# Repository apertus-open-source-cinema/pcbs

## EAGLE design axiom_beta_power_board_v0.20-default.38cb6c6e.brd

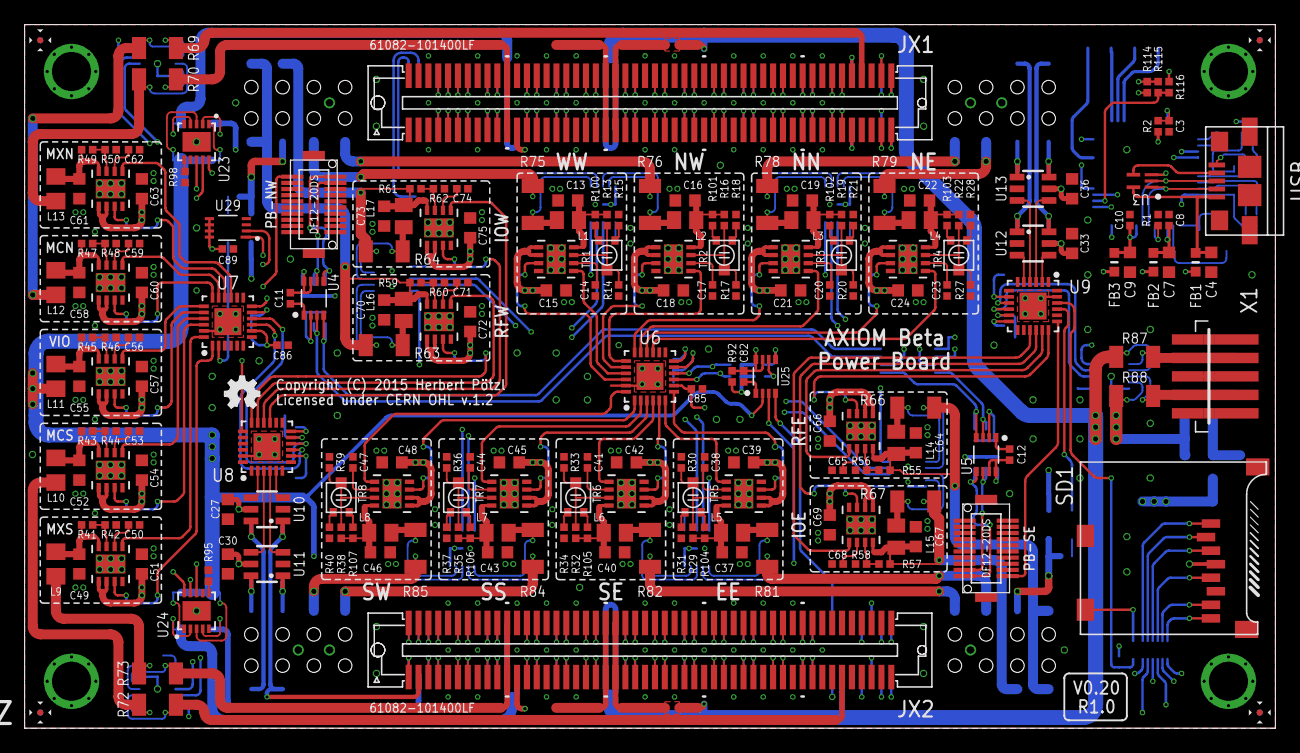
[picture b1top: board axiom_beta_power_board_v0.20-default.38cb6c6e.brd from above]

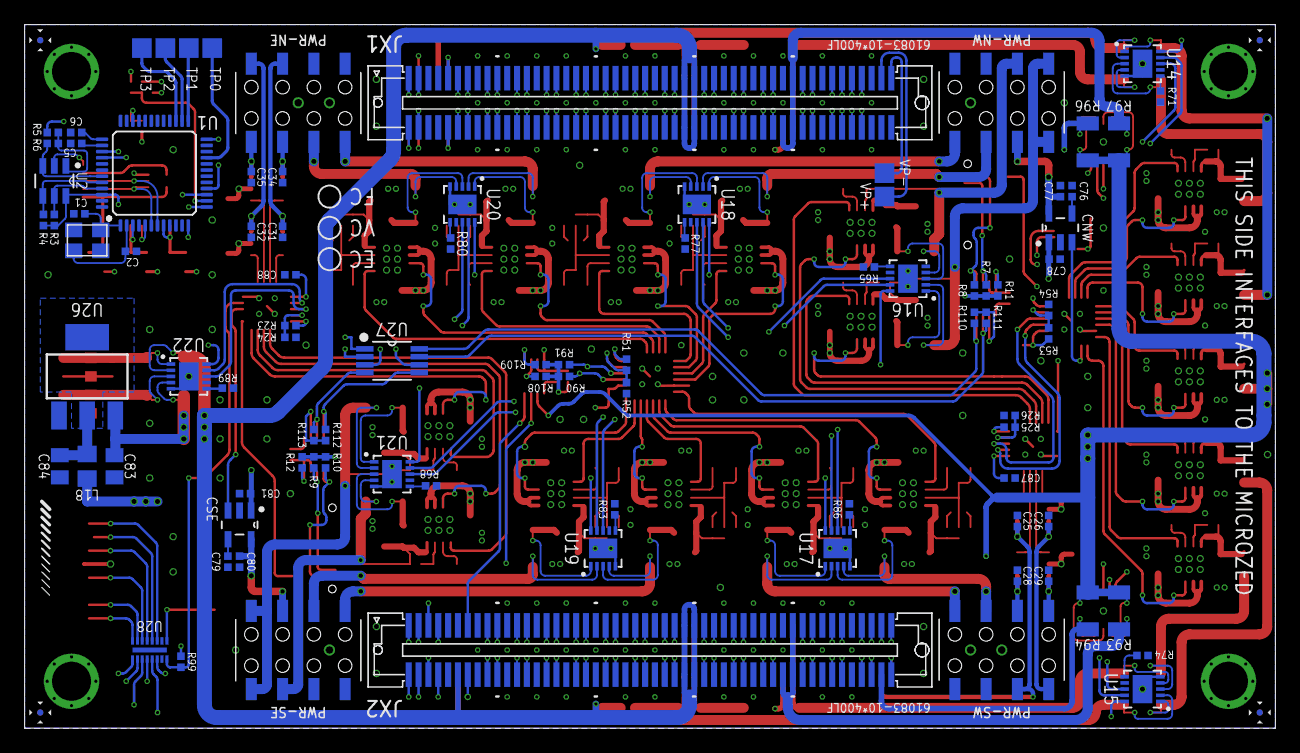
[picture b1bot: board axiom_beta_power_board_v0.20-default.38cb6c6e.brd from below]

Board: 4 copper layers, 101.6 x 57.1 mm, 301 parts (91 on the bottom side), 364 nets.

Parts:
BETA: µZ-FCI-SOCKET-NOHOLES-R; µZ-SOCKET-NOHOLES-R
C1, C2, C14, C17, C20, C23, C38, C41, C44, C47, C50, C53, C56, C59, C62, C65, C68, C71, C74: 0402-B
C3, C11, C12, C76, C79, C82: 10n; 0402-B
C4: 100n; 0603-B
C5, C6, C8, C10, C85, C86, C87, C88, C89: 100n; 0402-B
C7, C9, C27, C30, C33, C36: 4µ7; 0603-B
C13, C15, C16, C18, C19, C21, C22, C24, C37, C39, C40, C42, C43, C45, C46, C48, C49, C51, C52, C54, C55, C57, C58, C60, C61, C63, C64, C66, C67, C69, C73, C75: 0603-B
C25, C26, C28, C29, C31, C32, C34, C35, C77, C78, C80, C81: 1µ; 0402-B
C70, C72: 10µ; 0603-B
C83, C84: 22µ; 0805-B
CNW: SPX3819M5-L; SOT95P280X145-5N
CSE: SPX3819M5-L; SOT95P280X145-5N
EE: MCP1727-ADJE/MF; DFN65P300X300X100-9N
FB1, FB2, FB3: 600R; _0603MP
IOE: MCP1727-ADJE/MF; DFN65P300X300X100-9N
IOW: MCP1727-ADJE/MF; DFN65P300X300X100-9N
L1, L2, L3, L4, L5, L6, L7, L8, L14, L15, L16, L17: 0805-B
L9, L10, L11, L12, L13, L18: 0805-A
LOGO1: OSHW_LOGO_FILLX0100-NT; OSHW_FILLX100_NOTEXT
MCN: MCP1727-ADJE/MF; DFN65P300X300X100-9N
MCS: MCP1727-ADJE/MF; DFN65P300X300X100-9N
MXN: MCP1727-ADJE/MF; DFN65P300X300X100-9N
MXS: MCP1727-ADJE/MF; DFN65P300X300X100-9N
NE: MCP1727-ADJE/MF; DFN65P300X300X100-9N
NN: MCP1727-ADJE/MF; DFN65P300X300X100-9N
NW: MCP1727-ADJE/MF; DFN65P300X300X100-9N
PB-NW: DF12(XX)-20DP-0.5V
PB-SE: DF12(XX)-20DP-0.5V
PWR-NE: PINRC-2X04; R2X04
PWR-NW: PINRC-2X04; R2X04
PWR-SE: PINRC-2X04; R2X04
PWR-SW: PINRC-2X04; R2X04
Q1: SMD-4P-2G-3.2X2.5; ABM8G
R1: 12k; 0402-B
R2, R3, R4, R5, R24, R26, R99: 10k; 0402-B
R6: 2k; 0402-B
R7, R8, R9, R10, R90, R91, R108, R109, R110, R111, R112, R113: 4k7; 0402-B
R11, R12, R92: 200k; 0402-B
R13, R14, R15, R16, R17, R18, R19, R20, R21, R22, R27, R28, R29, R30, R31, R32, R33, R34, R35, R36, R37, R38, R39, R40, R41, R42, R43, R44, R45, R46, R47, R48, R49, R50, R55, R56, R57, R58, R59, R60, R61, R62, R100, R101, R102, R103, R104, R105, R106, R107: 0402-B
R23: 22k; 0402-B
R25, R51: 13k; 0402-B
R52: 3k; 0402-B
R53: 15k; 0402-B
R54: 1k; 0402-B
R63, R64, R66, R67, R69, R70, R72, R73, R75, R76, R78, R79, R81, R82, R84, R85, R87, R88, R93, R94, R96, R97: 1206-B
R65: 5k6; 0402-B
R68: 9k1; 0402-B
R71: 2k0; 0402-B
R74: 2k7; 0402-B
R77: 750R; 0402-B
R80: 1k27; 0402-B
R83, R114, R115, R116: 0R; 0402-B
R86: 100R; 0402-B
R89: 1k6; 0402-B
R95: 430R; 0402-B
R98: 560R; 0402-B
RFE: MCP1727-ADJE/MF; DFN65P300X300X100-9N
RFW: MCP1727-ADJE/MF; DFN65P300X300X100-9N
SD1: MICRO-SD-2CD; TF-MICRO-SD_PP2
SE: MCP1727-ADJE/MF; DFN65P300X300X100-9N
SS: MCP1727-ADJE/MF; DFN65P300X300X100-9N
SW: MCP1727-ADJE/MF; DFN65P300X300X100-9N
TP0, TP1, TP2, TP3: TPTP16SQ; TP16SQ
TR1, TR2, TR3, TR4, TR5, TR6, TR7, TR8: PVZ2A; TRIM-PVZ2A
U1: FT232H; LQFP48
U2: 93LC46BT-I/OT; SOT95P280X145-6N
U3: TPD3E001DRLR; SOT50P160X60-5N
U4, U5, U25: GTL2002DC; VSSOP-8
U6, U7, U8, U9: QFN50P400X400X80-25N
U10, U11, U12, U13: SOT23-6
U14, U15, U16, U17, U18, U19, U20, U21, U22, U23, U24: PAC1720; DFN3X3_10LEAD
U26: LD1117S; SOT-223
U27: PCA9540BDP; SOP65P490X110-8N
U28: IP4251CZ16-8-TTL; SON40P135X330X55-17N
U29: LM75BGD; SOT996-2/3
USB: 5_USB_3S; MICRO-AB-H-SMT
VIO: MCP1727-ADJE/MF; DFN65P300X300X100-9N
VP+: TPTP16SQ; TP16SQ
VP-: TPTP16SQ; TP16SQ
WW: MCP1727-ADJE/MF; DFN65P300X300X100-9N
X1: PICO-SPOX-5
ZED: µZ-FCI-CONONLY; µZ-CONONLY

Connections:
AB_SCL: U25.4, ZED.113
AB_SCL': R109.2, U25.5, U27.1
AB_SDA: U25.3, ZED.114
AB_SDA': R108.2, U25.6, U27.2
A_!SS: PB-NW.1, U8.19
A_SCL: PB-NW.2, R8.2, U4.5
A_SCL': R110.2, U4.4, U27.8
A_SDA: PB-NW.4, R7.2, U4.6
A_SDA': R111.2, U4.3, U27.7
BANK13_00_N: BETA.89, ZED.89
BANK13_00_P: BETA.87, ZED.87
BANK13_01_N: BETA.90, ZED.90
BANK13_01_P: BETA.88, ZED.88
BANK13_02_N: BETA.93, ZED.93
BANK13_02_P: BETA.91, ZED.91
BANK13_03_N: BETA.94, ZED.94
BANK13_03_P: BETA.92, ZED.92
BANK13_04_N: BETA.195, ZED.195
BANK13_04_P: BETA.193, ZED.193
BANK13_05_N: BETA.196, ZED.196
BANK13_05_P: BETA.194, ZED.194
BANK13_06_N: BETA.199, ZED.199
BANK13_06_P: BETA.197, ZED.197
BANK13_SE_0: BETA.200, ZED.200
BETA_5V: R88.1, U22.3, X1.4, X1.4A
BETA_5V': C15.1, C18.1, C21.1, C24.1, C27.1, C30.1, C33.1, C36.1, C39.1, C42.1, C45.1, C48.1, C51.1, C54.1, C57.1, C60.1, C63.1, C66.1, C69.1, C72.1, C75.1, C78.1, C81.1, C83.1, CNW.1, CSE.1, EE.1, EE.2, IOE.1, IOE.2, IOW.1, IOW.2, MCN.1, MCN.2, MCS.1, MCS.2, MXN.1, MXN.2, MXS.1, MXS.2, NE.1, NE.2, NN.1, NN.2, NW.1, NW.2, R88.2, RFE.1, RFE.2, RFW.1, RFW.2, SE.1, SE.2, SS.1, SS.2, SW.1, SW.2, U10.5, U11.5, U12.5, U13.5, U22.4, U26.3, VIO.1, VIO.2, WW.1, WW.2
BETA_TDI: BETA.4, R116.2
BETA_TDO: BETA.3, R114.1
B_!SS: PB-SE.1, U9.19
B_SCL: PB-SE.2, R10.2, U5.5
B_SCL': R112.2, U5.4, U27.5
B_SDA: PB-SE.4, R9.2, U5.6
B_SDA': R113.2, U5.3, U27.4
CD: SD1.CD1, U28.1
CD': R99.2, U9.22, U28.16
CLK: SD1.5, U28.6
CMD: SD1.3, U28.5
CNW_EN: CNW.3, U7.2
CSE_EN: CSE.3, U9.21
CSO_NE_V: BETA.7, R69.2, U14.2
CSO_NW_V: C77.1, CNW.5, PWR-NW.6
CSO_N_V': L12.2, R69.1, U14.1
CSO_SE_V: C80.1, CSE.5, PWR-SE.6
CSO_SW_V: BETA.112, R72.2, U15.2
CSO_S_V': L10.2, R72.1, U15.1
DAT0: SD1.7, U28.7
DAT1: SD1.8, U28.8
DAT2: SD1.1, U28.3
DAT3: SD1.2, U28.4
EE_CLK1: R4.1, U1.44, U2.4
EE_CS1: R3.1, U1.45, U2.5
EE_DATA1: R6.2, U1.43, U2.3
EE_EN: EE.3, U6.7
EE_PG: EE.5, U6.6
E_I2C_EN: U9.5, U12.3
E_I2C_V: C31.1, PWR-NE.6, U12.1
E_SPI_EN: U9.2, U12.4
E_SPI_V: C32.1, PWR-NE.8, U12.6
E_VE: PWR-SE.4, R81.2, U19.2
E_VE': L5.2, R81.1, U19.1
FTDI_D_N: U1.6, U3.1, USB.2
FTDI_D_P: U1.7, U3.2, USB.3
FTDI_TCK: BETA.1, U1.13, ZED.1
FTDI_TDI: R115.1, R116.1, U1.14
FTDI_TDO: U1.15, ZED.3
FTDI_TMS: BETA.2, U1.16, ZED.2
GND: BETA.15, BETA.16, BETA.21, BETA.22, BETA.27, BETA.28, BETA.33, BETA.34, BETA.39, BETA.40, BETA.45, BETA.46, BETA.51, BETA.52, BETA.65, BETA.66, BETA.71, BETA.72, BETA.77, BETA.85, BETA.86, BETA.95, BETA.96, BETA.115, BETA.116, BETA.121, BETA.122, BETA.127, BETA.128, BETA.133, BETA.134, BETA.139, BETA.140, BETA.145, BETA.146, BETA.151, BETA.152, BETA.165, BETA.166, BETA.171, BETA.172, BETA.177, BETA.185, BETA.186, BETA.191, BETA.192, C1.2, C2.2, C3.2, C4.2, C5.2, C6.2, C7.2, C8.2, C9.2, C10.2, C11.2, C12.2, C13.2, C14.2, C15.2, C16.2, C17.2, C18.2, C19.2, C20.2, C21.2, C22.2, C23.2, C24.2, C25.2, C26.2, C27.2, C28.2, C29.2, C30.2, C31.2, C32.2, C33.2, C34.2, C35.2, C36.2, C37.2, C38.2, C39.2, C40.2, C41.2, C42.2, C43.2, C44.2, C45.2, C46.2, C47.2, C48.2, C49.2, C50.2, C51.2, C52.2, C53.2, C54.2, C55.2, C56.2, C57.2, C58.2, C59.2, C60.2, C61.2, C62.2, C63.2, C64.2, C65.2, C66.2, C67.2, C68.2, C69.2, C70.2, C71.2, C72.2, C73.2, C74.2, C75.2, C76.2, C77.2, C78.2, C79.2, C80.2, C81.2, C82.2, C83.2, C84.2, C85.2, C86.2, C87.2, C88.2, C89.2, CNW.2, CSE.2, EE.4, EE.9, IOE.4, IOE.9, IOW.4, IOW.9, MCN.4, MCN.9, MCS.4, MCS.9, MXN.4, MXN.9, MXS.4, MXS.9, NE.4, NE.9, NN.4, NN.9, NW.4, NW.9, PB-NW.6, PB-SE.6, PWR-NE.2, PWR-NE.4, PWR-NW.1, PWR-NW.3, PWR-SE.1, PWR-SE.3, PWR-SW.2, PWR-SW.4, Q1.2, Q1.4, R1.1, R14.2, R15.2, R17.2, R18.2, R20.2, R21.2, R24.2, R26.2, R27.2, R28.2, R30.2, R31.2, R33.2, R34.2, R36.2, R37.2, R39.2, R40.2, R42.2, R44.2, R46.2, R48.2, R50.2, R52.2, R54.2, R56.2, R58.2, R60.2, R62.2, R65.2, R68.2, R71.2, R74.2, R77.2, R80.2, R83.2, R86.2, R89.2, R95.2, R98.2, RFE.4, RFE.9, RFW.4, RFW.9, SD1.6, SD1.CD2, SD1.MT1, SD1.MT2, SE.4, SE.9, SS.4, SS.9, SW.4, SW.9, U1.4, U1.9, U1.10, U1.11, U1.22, U1.23, U1.35, U1.36, U1.41, U1.47, U1.48, U2.2, U3.3, U4.1, U5.1, U6.23, U6.25, U7.23, U7.25, U8.23, U8.25, U9.23, U9.25, U10.2, U11.2, U12.2, U13.2, U14.5, U14.EPAD, U15.5, U15.EPAD, U16.5, U16.EPAD, U17.5, U17.EPAD, U18.5, U18.EPAD, U19.5, U19.EPAD, U20.5, U20.EPAD, U21.5, U21.EPAD, U22.5, U22.EPAD, U23.5, U23.EPAD, U24.5, U24.EPAD, U25.1, U26.1, U27.6, U28.17, U29.4, USB.5, VIO.4, VIO.9, WW.4, WW.9, X1.1, X1.1A, X1.5, X1.5A, ZED.15, ZED.16, ZED.21, ZED.22, ZED.27, ZED.28, ZED.33, ZED.34, ZED.39, ZED.40, ZED.45, ZED.46, ZED.51, ZED.52, ZED.65, ZED.66, ZED.71, ZED.72, ZED.77, ZED.85, ZED.86, ZED.95, ZED.96, ZED.115, ZED.116, ZED.121, ZED.122, ZED.127, ZED.128, ZED.133, ZED.134, ZED.139, ZED.140, ZED.145, ZED.146, ZED.151, ZED.152, ZED.165, ZED.166, ZED.171, ZED.172, ZED.177, ZED.185, ZED.186, ZED.191, ZED.192
IOE_EN: IOE.3, U9.16
IOE_PG: IOE.5, U9.15
IOE_V: PWR-SE.5, R9.1, R10.1, R12.1, R67.2, U21.4
IOE_V': L15.2, R67.1, U21.3
IOW_EN: IOW.3, U8.16
IOW_PG: IOW.5, U8.15
IOW_V: PWR-NW.5, R7.1, R8.1, R11.1, R64.2, U16.4
IOW_V': L17.2, R64.1, U16.3
JTAG_EN: U8.2, U10.4
JTAG_V: C26.1, PWR-SW.8, U10.6
JX1_00_N: BETA.13, ZED.13
JX1_00_P: BETA.11, ZED.11
JX1_01_N: BETA.14, ZED.14
JX1_01_P: BETA.12, ZED.12
JX1_02_N: BETA.19, ZED.19
JX1_02_P: BETA.17, ZED.17
JX1_03_N: BETA.20, ZED.20
JX1_03_P: BETA.18, ZED.18
JX1_04_N: BETA.25, ZED.25
JX1_04_P: BETA.23, ZED.23
JX1_05_N: BETA.26, ZED.26
JX1_05_P: BETA.24, ZED.24
JX1_06_N: BETA.31, ZED.31
JX1_06_P: BETA.29, ZED.29
JX1_07_N: BETA.32, ZED.32
JX1_07_P: BETA.30, ZED.30
JX1_08_N: BETA.37, ZED.37
JX1_08_P: BETA.35, ZED.35
JX1_09_N: BETA.38, ZED.38
JX1_09_P: BETA.36, ZED.36
JX1_10_N: BETA.43, ZED.43
JX1_10_P: BETA.41, ZED.41
JX1_11_N: BETA.44, ZED.44
JX1_11_P: BETA.42, ZED.42
JX1_12_N: BETA.49, ZED.49
JX1_12_P: BETA.47, ZED.47
JX1_13_N: BETA.50, ZED.50
JX1_13_P: BETA.48, ZED.48
JX1_14_N: BETA.55, ZED.55
JX1_14_P: BETA.53, ZED.53
JX1_15_N: BETA.56, ZED.56
JX1_15_P: BETA.54, ZED.54
JX1_16_N: BETA.63, ZED.63
JX1_16_P: BETA.61, ZED.61
JX1_17_N: BETA.64, ZED.64
JX1_17_P: BETA.62, ZED.62
JX1_18_N: BETA.69, ZED.69
JX1_18_P: BETA.67, ZED.67
JX1_19_N: BETA.70, ZED.70
JX1_19_P: BETA.68, ZED.68
JX1_20_N: BETA.75, ZED.75
JX1_20_P: BETA.73, ZED.73
JX1_21_N: BETA.76, ZED.76
JX1_21_P: BETA.74, ZED.74
JX1_22_N: BETA.83, ZED.83
JX1_22_P: BETA.81, ZED.81
JX1_23_N: BETA.84, ZED.84
JX1_23_P: BETA.82, ZED.82
JX2_00_N: BETA.119, ZED.119
JX2_00_P: BETA.117, ZED.117
JX2_01_N: BETA.120, ZED.120
JX2_01_P: BETA.118, ZED.118
JX2_02_N: BETA.125, ZED.125
JX2_02_P: BETA.123, ZED.123
JX2_03_N: BETA.126, ZED.126
JX2_03_P: BETA.124, ZED.124
JX2_04_N: BETA.131, ZED.131
JX2_04_P: BETA.129, ZED.129
JX2_05_N: BETA.132, ZED.132
JX2_05_P: BETA.130, ZED.130
JX2_06_N: BETA.137, ZED.137
JX2_06_P: BETA.135, ZED.135
JX2_07_N: BETA.138, ZED.138
JX2_07_P: BETA.136, ZED.136
JX2_08_N: BETA.143, ZED.143
JX2_08_P: BETA.141, ZED.141
JX2_09_N: BETA.144, ZED.144
JX2_09_P: BETA.142, ZED.142
JX2_10_N: BETA.149, ZED.149
JX2_10_P: BETA.147, ZED.147
JX2_11_N: BETA.150, ZED.150
JX2_11_P: BETA.148, ZED.148
JX2_12_N: BETA.155, ZED.155
JX2_12_P: BETA.153, ZED.153
JX2_13_N: BETA.156, ZED.156
JX2_13_P: BETA.154, ZED.154
JX2_14_N: BETA.163, ZED.163
JX2_14_P: BETA.161, ZED.161
JX2_15_N: BETA.164, ZED.164
JX2_15_P: BETA.162, ZED.162
JX2_16_N: BETA.169, ZED.169
JX2_16_P: BETA.167, ZED.167
JX2_17_N: BETA.170, ZED.170
JX2_17_P: BETA.168, ZED.168
JX2_18_N: BETA.175, ZED.175
JX2_18_P: BETA.173, ZED.173
JX2_19_N: BETA.176, ZED.176
JX2_19_P: BETA.174, ZED.174
JX2_20_N: BETA.183, ZED.183
JX2_20_P: BETA.181, ZED.181
JX2_21_N: BETA.184, ZED.184
JX2_21_P: BETA.182, ZED.182
JX2_22_N: BETA.189, ZED.189
JX2_22_P: BETA.187, ZED.187
JX2_23_N: BETA.190, ZED.190
JX2_23_P: BETA.188, ZED.188
MCN_EN: MCN.3, U7.18
MCN_PG: MCN.5, U7.17
MCS_EN: MCS.3, U7.22
MCS_PG: MCS.5, U7.21
MXN_EN: MXN.3, U7.16
MXN_PG: MXN.5, U7.15
MXS_EN: MXS.3, U7.1
MXS_PG: MXS.5, U7.24
unnamed: C49.1, L9.1, MXS.8, R41.1
unnamed: R77.1, U18.6
unnamed: C11.1, R11.2, U4.7, U4.8
unnamed: C12.1, R12.2, U5.7, U5.8
unnamed: C13.1, L1.1, R13.1, R100.2, WW.8
unnamed: TP1.TP, U1.25
unnamed: TP2.TP, U1.26
unnamed: R95.1, U24.6
unnamed: R13.2, R14.1, TR1.2, WW.7
unnamed: R15.1, TR1.1
unnamed: MXS.7, R41.2, R42.1
unnamed: C50.1, MXS.6
unnamed: C64.1, L14.1, R55.1, RFE.8
unnamed: R55.2, R56.1, RFE.7
unnamed: R98.1, U23.6
unnamed: TP3.TP, U1.27
unnamed: C14.1, WW.6
unnamed: C65.1, RFE.6
unnamed: C67.1, IOE.8, L15.1, R57.1
unnamed: TP0.TP, U1.21
unnamed: R5.1, R6.1, U2.1
unnamed: C1.1, Q1.1, U1.1
unnamed: C2.1, Q1.3, U1.2
unnamed: C3.1, R2.1, U1.34
unnamed: R1.2, U1.5
unnamed: U3.4, USB.4
unnamed: R23.2, R24.1, U9.11
unnamed: R25.2, R26.1, U8.11
unnamed: R100.1, TR1.3
unnamed: C16.1, L2.1, NW.8, R16.1, R101.2
unnamed: NW.7, R16.2, R17.1, TR2.2
unnamed: R18.1, TR2.1
unnamed: C17.1, NW.6
unnamed: IOE.7, R57.2, R58.1
unnamed: C68.1, IOE.6
unnamed: R80.1, U20.6
unnamed: C19.1, L3.1, NN.8, R19.1, R102.2
unnamed: NN.7, R19.2, R20.1, TR3.2
unnamed: R101.1, TR2.3
unnamed: C20.1, NN.6
unnamed: C70.1, L16.1, R59.1, RFW.8
unnamed: R59.2, R60.1, RFW.7
unnamed: R83.1, U19.6
unnamed: C22.1, L4.1, NE.8, R22.1, R103.2
unnamed: NE.7, R22.2, R27.1, TR4.2
unnamed: R21.1, TR3.1
unnamed: C23.1, NE.6
unnamed: C71.1, RFW.6
unnamed: C73.1, IOW.8, L17.1, R61.1
unnamed: R86.1, U17.6
unnamed: C37.1, EE.8, L5.1, R29.1, R104.2
unnamed: EE.7, R29.2, R30.1, TR5.2
unnamed: R102.1, TR3.3
unnamed: C38.1, EE.6
unnamed: IOW.7, R61.2, R62.1
unnamed: C74.1, IOW.6
unnamed: R28.1, TR4.1
unnamed: R65.1, U16.6
unnamed: C40.1, L6.1, R32.1, R105.2, SE.8
unnamed: R32.2, R33.1, SE.7, TR6.2
unnamed: R103.1, TR4.3
unnamed: C41.1, SE.6
unnamed: C82.1, R92.2, U25.7, U25.8
unnamed: R31.1, TR5.1
unnamed: C43.1, L7.1, R35.1, R106.2, SS.8
unnamed: R35.2, R36.1, SS.7, TR7.2
unnamed: R104.1, TR5.3
unnamed: C44.1, SS.6
unnamed: R34.1, TR6.1
unnamed: R68.1, U21.6
unnamed: C46.1, L8.1, R38.1, R107.2, SW.8
unnamed: R38.2, R39.1, SW.7, TR8.2
unnamed: R105.1, TR6.3
unnamed: C47.1, SW.6
unnamed: R37.1, TR7.1
unnamed: R71.1, U14.6
unnamed: R106.1, TR7.3
unnamed: R74.1, U15.6
unnamed: C52.1, L10.1, MCS.8, R43.1
unnamed: MCS.7, R43.2, R44.1
unnamed: C53.1, MCS.6
unnamed: R40.1, TR8.1
unnamed: R89.1, U22.6
unnamed: C55.1, L11.1, R45.1, VIO.8
unnamed: R45.2, R46.1, VIO.7
unnamed: C56.1, VIO.6
unnamed: R107.1, TR8.3
unnamed: C58.1, L12.1, MCN.8, R47.1
unnamed: MCN.7, R47.2, R48.1
unnamed: C59.1, MCN.6
unnamed: C76.1, CNW.4
unnamed: C61.1, L13.1, MXN.8, R49.1
unnamed: MXN.7, R49.2, R50.1
unnamed: C62.1, MXN.6
unnamed: R51.2, R52.1, U6.11
unnamed: R53.2, R54.1, U7.11
unnamed: C79.1, CSE.4
NE_EN: NE.3, U6.16
NE_PG: NE.5, U6.15
NN_EN: NN.3, U6.18
NN_PG: NN.5, U6.17
NW_EN: NW.3, U6.20
NW_PG: NW.5, U6.19
N_I2C_EN: U9.3, U13.4
N_I2C_V: C35.1, PWR-NE.7, U13.6
N_SPI_EN: U9.4, U13.3
N_SPI_V: C34.1, PWR-NE.5, U13.1
N_VE: PWR-NE.3, R79.2, U20.4
N_VE': L4.2, R79.1, U20.3
N_VN: PWR-NE.1, R78.2, U20.2
N_VN': L3.2, R78.1, U20.1
N_VW: PWR-NW.2, R76.2, U18.4
N_VW': L2.2, R76.1, U18.3
PCIE_N_5V: BETA.59, BETA.60
PCIE_N_V: BETA.79, BETA.80, R70.2, U14.4
PCIE_N_V': L13.2, R70.1, U14.3
PCIE_S_5V: BETA.159, BETA.160
PCIE_S_V: BETA.179, BETA.180, R73.2, U15.4
PCIE_S_V': L9.2, R73.1, U15.3
PCIE_VCCIO: R96.2, U23.2
PEX_N_V: BETA.57, BETA.58
PEX_S_V: BETA.157, BETA.158
PMOD_D0: U28.9, ZED.101
PMOD_D1: U28.10, ZED.102
PMOD_D2: U28.12, ZED.103
PMOD_D3: U28.11, ZED.104
PMOD_D6: U28.14, ZED.107
PMOD_D7: U28.13, ZED.108
PMOD_SCL: R90.2, U6.9, U7.9, U8.9, U9.9, U14.9, U15.9, U16.9, U17.9, U18.9, U19.9, U20.9, U21.9, U22.9, U23.9, U24.9, U29.2, ZED.105
PMOD_SDA: R91.2, U6.10, U7.10, U8.10, U9.10, U14.8, U15.8, U16.8, U17.8, U18.8, U19.8, U20.8, U21.8, U22.8, U23.8, U24.8, U29.1, ZED.106
REGOUT: C84.1, L18.1, U26.2, U26.TER
RFE_EN: RFE.3, U9.18
RFE_PG: RFE.5, U9.17
RFE_V: PWR-SE.7, R66.2, U21.2
RFE_V': L14.2, R66.1, U21.1
RFW_EN: RFW.3, U8.18
RFW_PG: RFW.5, U8.17
RFW_V: PWR-NW.7, R63.2, U16.2
RFW_V': L16.2, R63.1, U16.1
SE_0: BETA.9, ZED.9
SE_1: BETA.10, ZED.10
SE_EN: SE.3, U6.5
SE_PG: SE.5, U6.4
SS_EN: SS.3, U6.3
SS_PG: SS.5, U6.2
SW_EN: SW.3, U6.1
SW_PG: SW.5, U6.24
S_I2C_EN: U8.3, U11.4
S_I2C_V: C29.1, PWR-SW.7, U11.6
S_SPI_EN: U8.4, U11.3
S_SPI_V: C28.1, PWR-SW.5, U11.1
S_VE: PWR-SE.2, R82.2, U19.4
S_VE': L6.2, R82.1, U19.3
S_VS: PWR-SW.1, R84.2, U17.2
S_VS': L7.2, R84.1, U17.1
S_VW: PWR-SW.3, R85.2, U17.4
S_VW': L8.2, R85.1, U17.3
VBUS: C4.1, FB1.1, U3.5, USB.1
VCC: C85.1, C86.1, C87.1, C88.1, C89.1, L18.2, R23.1, R25.1, R51.1, R53.1, R90.1, R91.1, R92.1, R99.1, R108.1, R109.1, R110.1, R111.1, R112.1, R113.1, SD1.4, U4.2, U5.2, U6.8, U6.12, U7.8, U7.12, U8.8, U8.12, U9.8, U9.12, U14.10, U15.10, U16.10, U17.10, U18.10, U19.10, U20.10, U21.10, U22.10, U23.10, U24.10, U27.3, U29.5, U29.6, U29.7, U29.8
VCCA: C6.1, U1.37
VCCD: FB2.1, FB3.1, R2.2, R3.2, R4.2, R5.2, U1.12, U1.24, U1.39, U1.46, U2.6
VCCIO: L11.2, R93.1, R94.1, R96.1, R97.1, U23.1, U23.3, U24.1, U24.3, U25.2
VCCO_13: R94.2, U24.4, ZED.198
VCCO_34: R97.2, U23.4, ZED.78, ZED.79, ZED.80
VCCO_35: R93.2, U24.2, ZED.178, ZED.179, ZED.180
VCORE: C5.1, U1.38
VIN: X1.3, X1.3A
VIO_EN: U7.20, VIO.3
VIO_PG: U7.19, VIO.5
VPHY: C7.1, C8.1, FB2.2, U1.3
VPLL: C9.1, C10.1, FB3.2, U1.8
VP_0_N: VP-.TP, ZED.99
VP_0_P: VP+.TP, ZED.97
VREGIN: FB1.2, U1.40
WW_EN: U6.22, WW.3
WW_PG: U6.21, WW.5
W_I2C_EN: U8.5, U10.3
W_I2C_V: C25.1, PWR-SW.6, U10.1
W_VW: PWR-NW.4, R75.2, U18.2
W_VW': L1.2, R75.1, U18.1
ZED_5V: R87.1, U22.1, X1.2, X1.2A
ZED_5V': R87.2, U22.2, ZED.57, ZED.58, ZED.59, ZED.60, ZED.112, ZED.157, ZED.158, ZED.159, ZED.160
ZED_TDI: R114.2, R115.2, ZED.4

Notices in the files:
axiom_beta_power_board_v0.20-default.38cb6c6e.brd:
Copyright (C) 2015 Herbert Pötzl
Licensed under CERN OHL v.1.2
parts and their libraries:
microbuilder: This work is placed in the public domain, and may be freely used for commercial and non-commercial work with the following conditions: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
